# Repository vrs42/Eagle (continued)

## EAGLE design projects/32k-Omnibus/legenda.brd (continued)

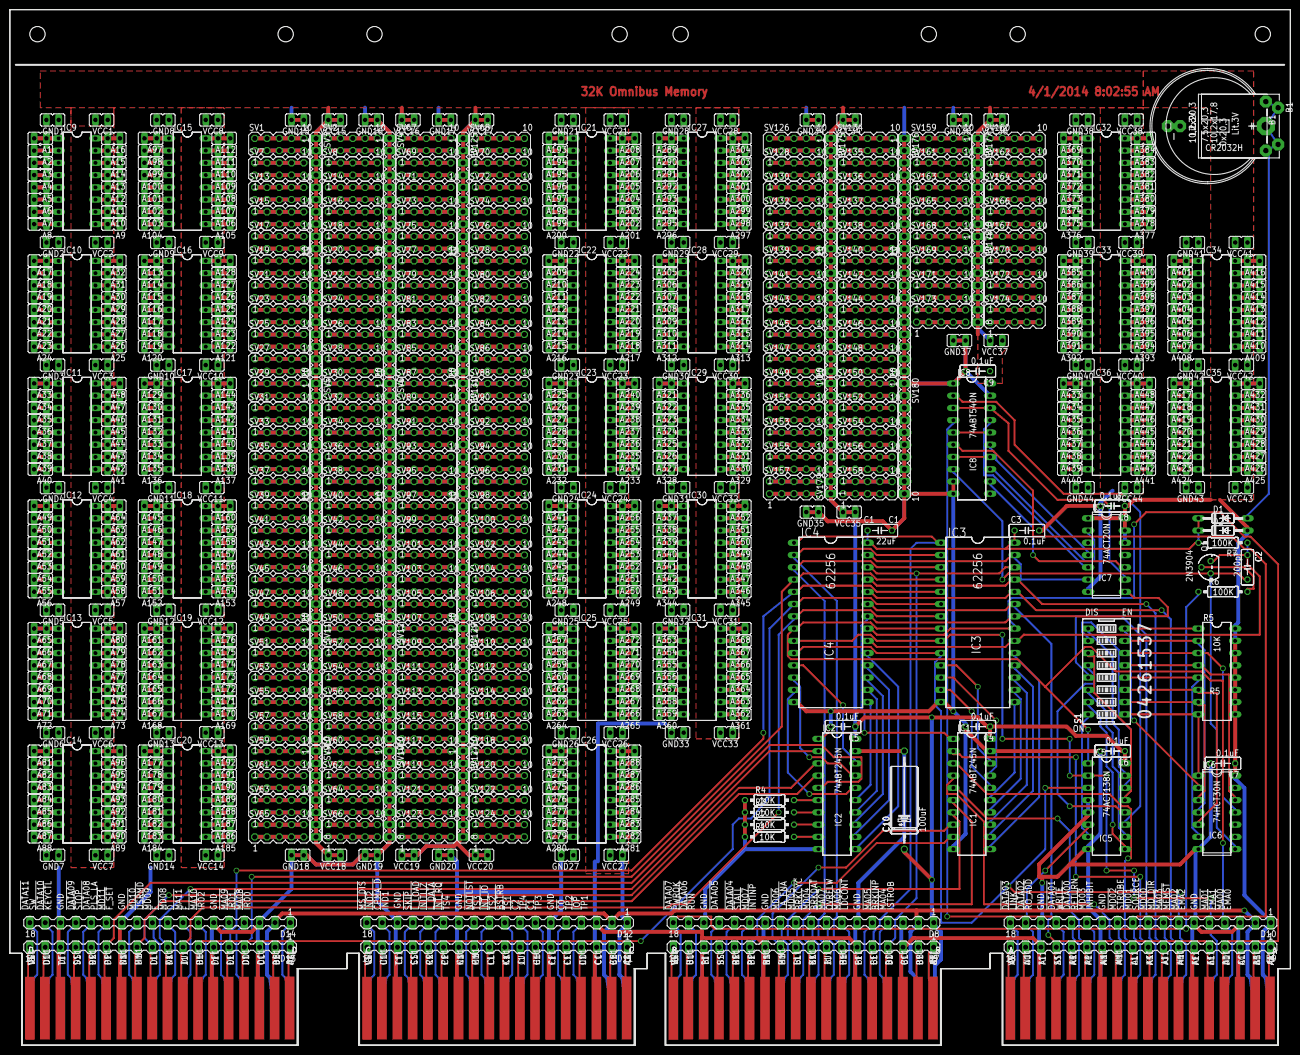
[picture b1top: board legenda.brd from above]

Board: 2 copper layers, 265.4 x 214.6 mm, 784 parts (0 on the bottom side), 930 nets.

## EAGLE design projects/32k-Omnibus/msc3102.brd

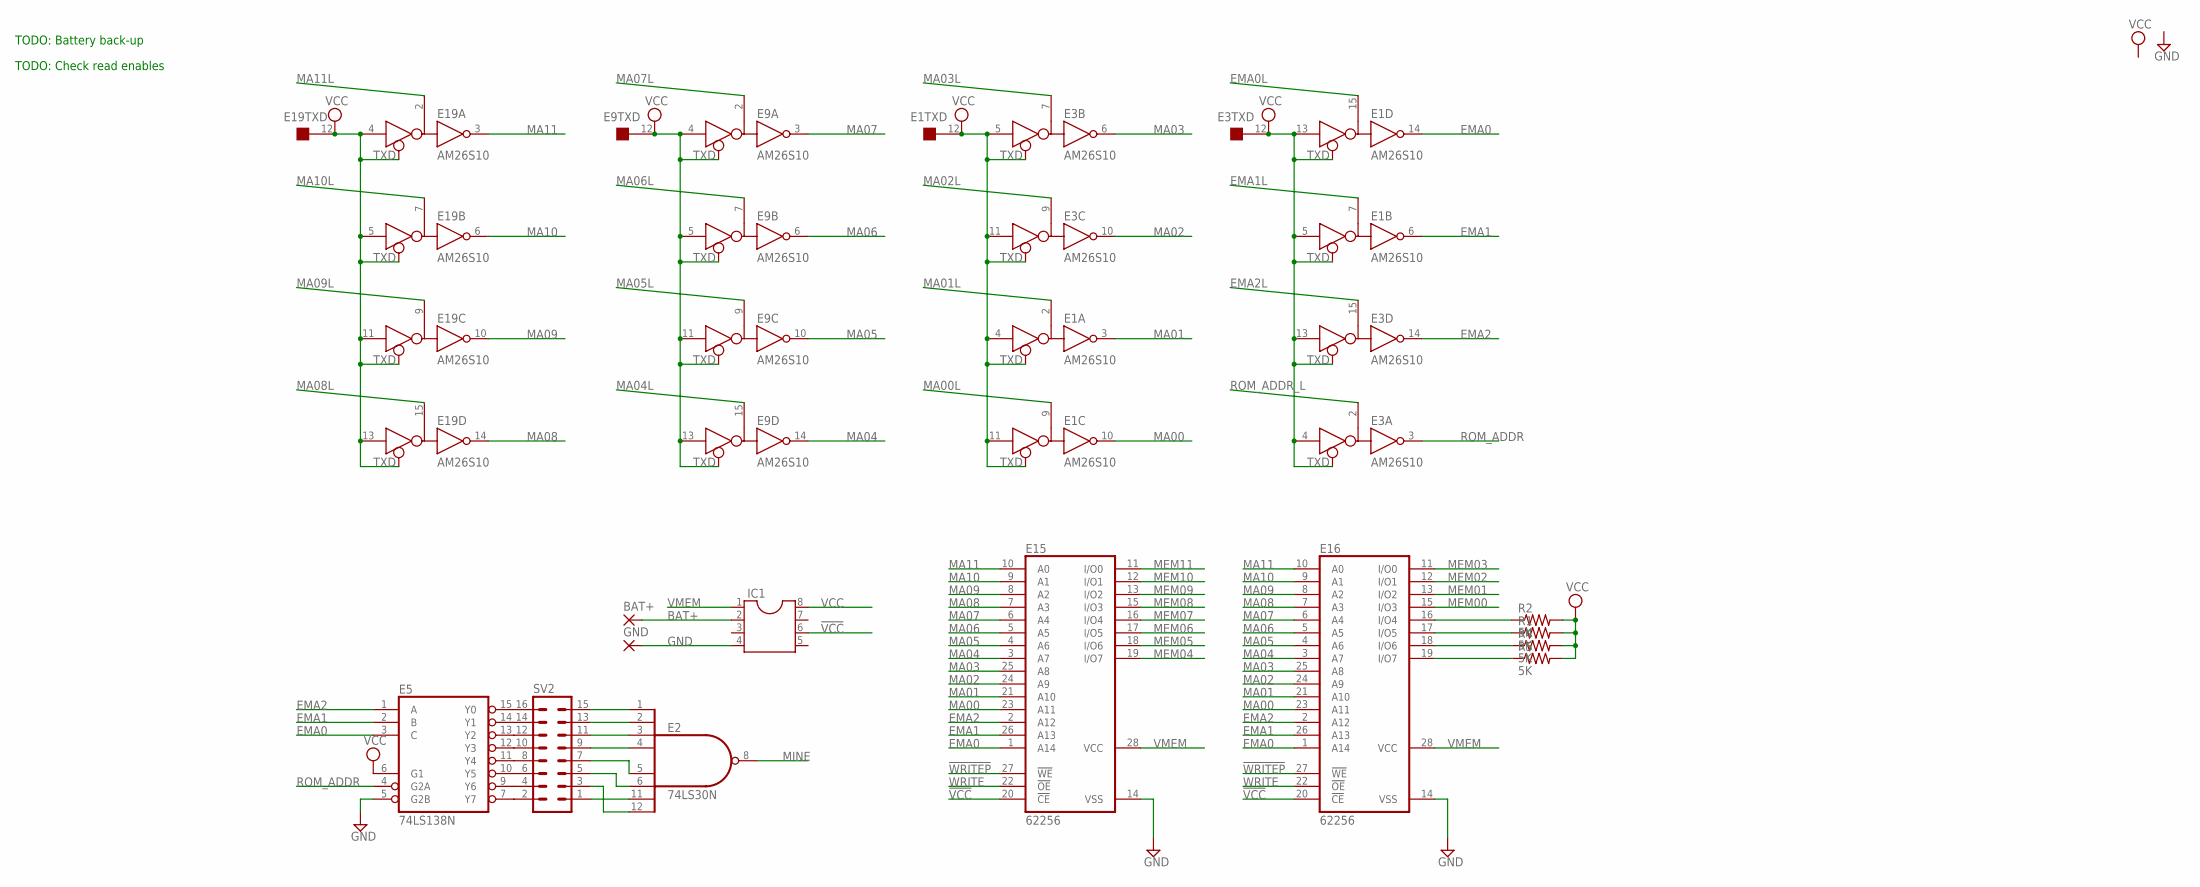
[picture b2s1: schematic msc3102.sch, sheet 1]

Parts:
BAT+: 2,15/1,0
E1, E3, E9, E19: AM26S10; DIL16
E2: 74LS30N; DIL14
E5: 74LS138N; DIL16
E15, E16: 62256; DIL28-6
GND: 2,15/1,0
IC1: DIL8; DIL08
R1, R2, R4, R5: 5K; 0207/10
SV2: MA08-2

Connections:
!VCC: E15.20 (!CE), E16.20 (!CE), IC1.6
!WRITEP: E15.27 (!WE), E16.27 (!WE); also elsewhere on the board
BAT+: BAT+.1, IC1.2
EMA0: E1.14 (R), E5.3 (C), E15.1 (A14), E16.1 (A14)
EMA0L: E1.15 (B); also elsewhere on the board
EMA1: E1.6 (R), E5.2 (B), E15.26 (A13), E16.26 (A13)
EMA1L: E1.7 (B); also elsewhere on the board
EMA2: E3.14 (R), E5.1 (A), E15.2 (A12), E16.2 (A12)
EMA2L: E3.15 (B); also elsewhere on the board
GND: E1.1 (GND), E1.8 (GND), E2.7 (GND), E3.1 (GND), E3.8 (GND), E5.5 (G2B), E5.8 (GND), E9.1 (GND), E9.8 (GND), E15.14 (VSS), E16.14 (VSS), E19.1 (GND), E19.8 (GND), GND.1, IC1.4; also elsewhere on the board
MA00: E1.10 (R), E15.23 (A11), E16.23 (A11)
MA00L: E1.9 (B); also elsewhere on the board
MA01: E1.3 (R), E15.21 (A10), E16.21 (A10)
MA01L: E1.2 (B); also elsewhere on the board
MA02: E3.10 (R), E15.24 (A9), E16.24 (A9)
MA02L: E3.9 (B); also elsewhere on the board
MA03: E3.6 (R), E15.25 (A8), E16.25 (A8)
MA03L: E3.7 (B); also elsewhere on the board
MA04: E9.14 (R), E15.3 (A7), E16.3 (A7)
MA04L: E9.15 (B); also elsewhere on the board
MA05: E9.10 (R), E15.4 (A6), E16.4 (A6)
MA05L: E9.9 (B); also elsewhere on the board
MA06: E9.6 (R), E15.5 (A5), E16.5 (A5)
MA06L: E9.7 (B); also elsewhere on the board
MA07: E9.3 (R), E15.6 (A4), E16.6 (A4)
MA07L: E9.2 (B); also elsewhere on the board
MA08: E15.7 (A3), E16.7 (A3), E19.14 (R)
MA08L: E19.15 (B); also elsewhere on the board
MA09: E15.8 (A2), E16.8 (A2), E19.10 (R)
MA09L: E19.9 (B); also elsewhere on the board
MA10: E15.9 (A1), E16.9 (A1), E19.6 (R)
MA10L: E19.7 (B); also elsewhere on the board
MA11: E15.10 (A0), E16.10 (A0), E19.3 (R)
MA11L: E19.2 (B); also elsewhere on the board
MEM00: E16.15 (I/O3); also elsewhere on the board
MEM01: E16.13 (I/O2); also elsewhere on the board
MEM02: E16.12 (I/O1); also elsewhere on the board
MEM03: E16.11 (I/O0); also elsewhere on the board
MEM04: E15.19 (I/O7); also elsewhere on the board
MEM05: E15.18 (I/O6); also elsewhere on the board
MEM06: E15.17 (I/O5); also elsewhere on the board
MEM07: E15.16 (I/O4); also elsewhere on the board
MEM08: E15.15 (I/O3); also elsewhere on the board
MEM09: E15.13 (I/O2); also elsewhere on the board
MEM10: E15.12 (I/O1); also elsewhere on the board
MEM11: E15.11 (I/O0); also elsewhere on the board
MINE: E2.8 (O); also elsewhere on the board
unnamed: E5.7 (Y7), SV2.2
unnamed: E5.9 (Y6), SV2.4
unnamed: E5.10 (Y5), SV2.6
unnamed: E5.11 (Y4), SV2.8
unnamed: E5.12 (Y3), SV2.10
unnamed: E5.13 (Y2), SV2.12
unnamed: E5.14 (Y1), SV2.14
unnamed: E5.15 (Y0), SV2.16
unnamed: E2.4 (I3), SV2.9
unnamed: E2.3 (I2), SV2.11
unnamed: E2.2 (I1), SV2.13
unnamed: E2.1 (I0), SV2.15
unnamed: E2.5 (I4), SV2.7
unnamed: E2.11 (I6), SV2.1
unnamed: E2.12 (I7), SV2.3
unnamed: E2.6 (I5), SV2.5
unnamed: E16.18 (I/O6), R4.1
unnamed: E16.16 (I/O4), R2.1
unnamed: E16.17 (I/O5), R1.1
unnamed: E16.19 (I/O7), R5.1
ROM_ADDR: E3.3 (R), E5.4 (G2A)
ROM_ADDR_L: E3.2 (B); also elsewhere on the board
VCC: E1.4 (D), E1.5 (D), E1.11 (D), E1.12 (TXD), E1.13 (D), E1.16 (VCC), E2.14 (VCC), E3.4 (D), E3.5 (D), E3.11 (D), E3.12 (TXD), E3.13 (D), E3.16 (VCC), E5.6 (G1), E5.16 (VCC), E9.4 (D), E9.5 (D), E9.11 (D), E9.12 (TXD), E9.13 (D), E9.16 (VCC), E19.4 (D), E19.5 (D), E19.11 (D), E19.12 (TXD), E19.13 (D), E19.16 (VCC), IC1.8, R1.2, R2.2, R4.2, R5.2; also elsewhere on the board
VMEM: E15.28 (VCC), E16.28 (VCC), IC1.1
WRITE: E15.22 (!OE), E16.22 (!OE); also elsewhere on the board

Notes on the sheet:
TODO: Battery back-up
TODO: Check read enables

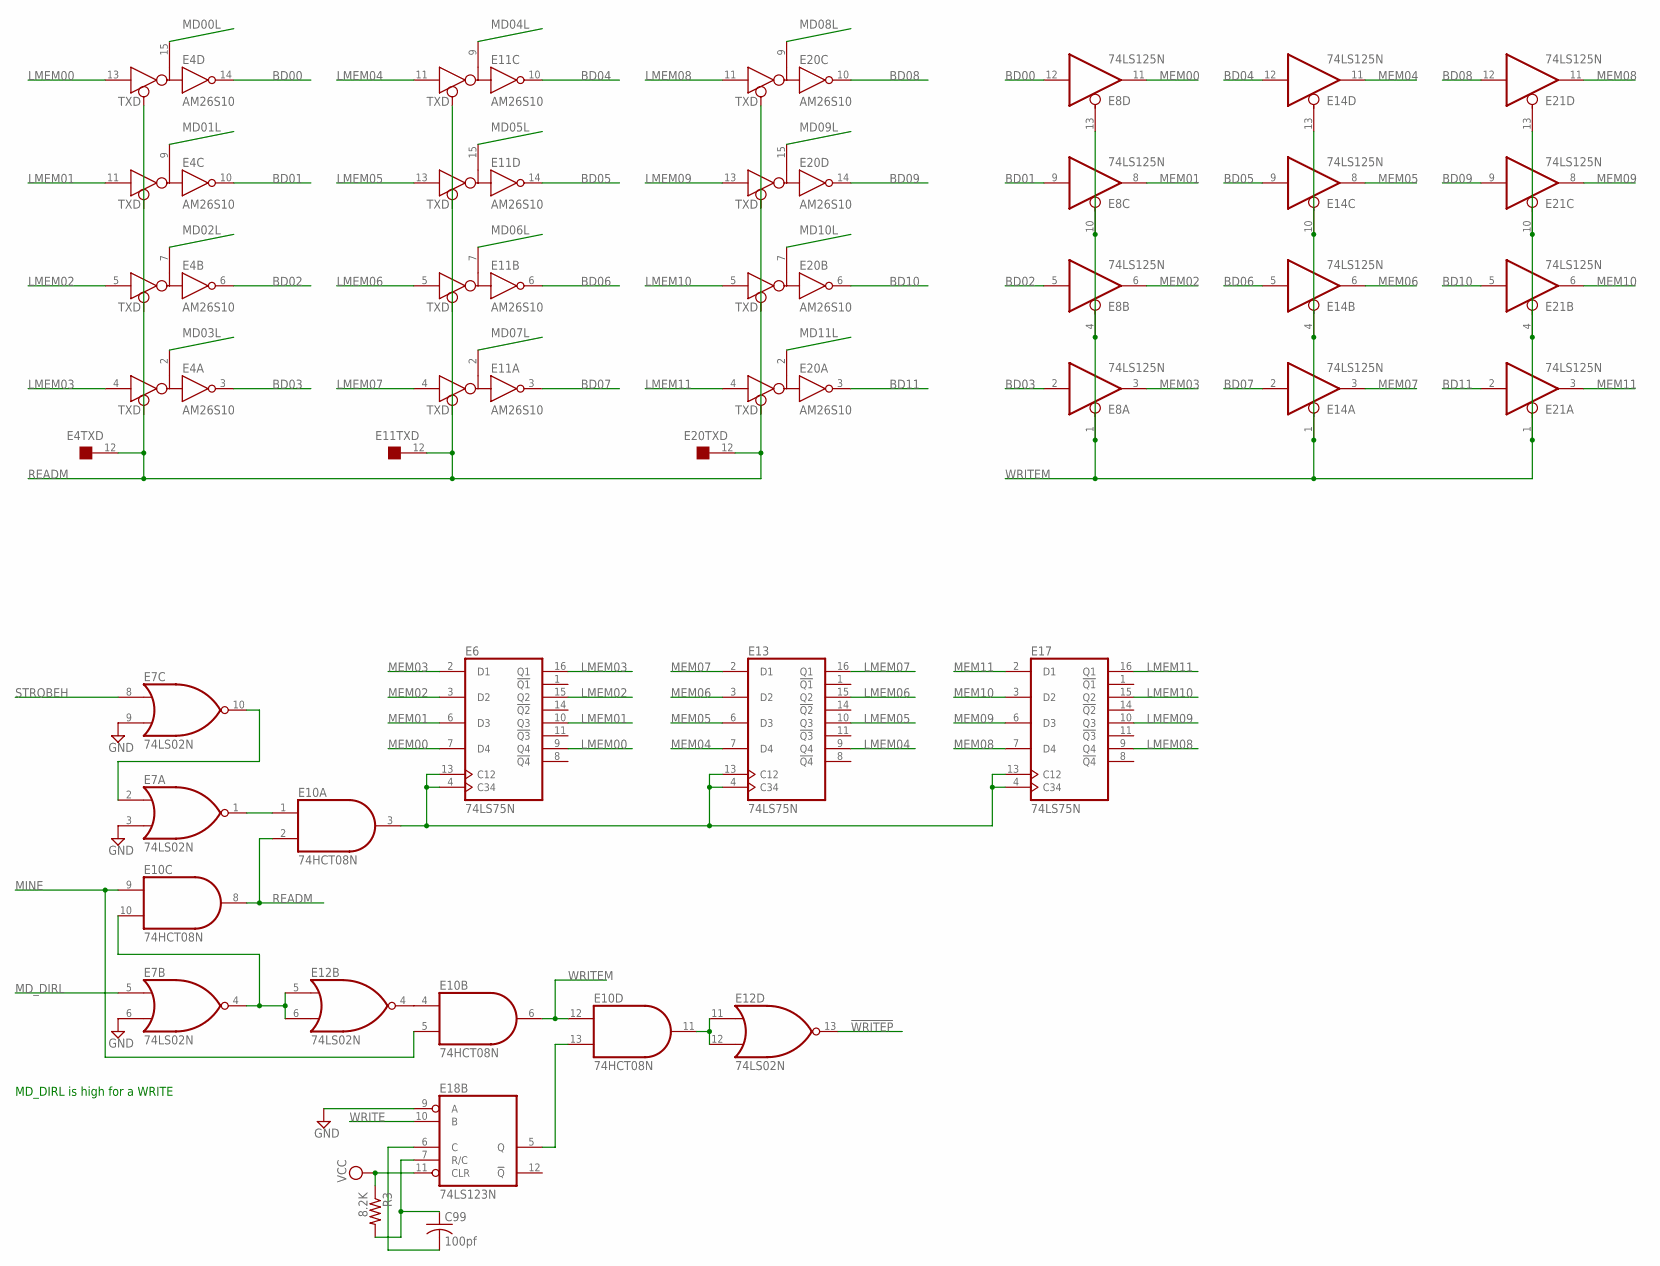
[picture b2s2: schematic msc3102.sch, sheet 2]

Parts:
C99: 100pf; C050-025X075
E4, E11, E20: AM26S10; DIL16
E6, E13, E17: 74LS75N; DIL16
E7, E12: 74LS02N; DIL14
E8, E14, E21: 74LS125N; DIL14
E10: 74HCT08N; DIL14
E18: 74LS123N; DIL16
R3: 8.2K; 0207/10

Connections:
!WRITEP: E12.13 (O); also elsewhere on the board
BD00: E4.14 (R), E8.12 (I)
BD01: E4.10 (R), E8.9 (I)
BD02: E4.6 (R), E8.5 (I)
BD03: E4.3 (R), E8.2 (I)
BD04: E11.10 (R), E14.12 (I)
BD05: E11.14 (R), E14.9 (I)
BD06: E11.6 (R), E14.5 (I)
BD07: E11.3 (R), E14.2 (I)
BD08: E20.10 (R), E21.12 (I)
BD09: E20.14 (R), E21.9 (I)
BD10: E20.6 (R), E21.5 (I)
BD11: E20.3 (R), E21.2 (I)
GND: E4.1 (GND), E4.8 (GND), E6.12 (GND), E7.3 (I1), E7.6 (I1), E7.7 (GND), E7.9 (I1), E8.7 (GND), E10.7 (GND), E11.1 (GND), E11.8 (GND), E12.7 (GND), E13.12 (GND), E14.7 (GND), E17.12 (GND), E18.8 (GND), E18.9 (A), E20.1 (GND), E20.8 (GND), E21.7 (GND); also elsewhere on the board
LMEM00: E4.13 (D), E6.9 (Q4)
LMEM01: E4.11 (D), E6.10 (Q3)
LMEM02: E4.5 (D), E6.15 (Q2)
LMEM03: E4.4 (D), E6.16 (Q1)
LMEM04: E11.11 (D), E13.9 (Q4)
LMEM05: E11.13 (D), E13.10 (Q3)
LMEM06: E11.5 (D), E13.15 (Q2)
LMEM07: E11.4 (D), E13.16 (Q1)
LMEM08: E17.9 (Q4), E20.11 (D)
LMEM09: E17.10 (Q3), E20.13 (D)
LMEM10: E17.15 (Q2), E20.5 (D)
LMEM11: E17.16 (Q1), E20.4 (D)
MD00L: E4.15 (B); also elsewhere on the board
MD01L: E4.9 (B); also elsewhere on the board
MD02L: E4.7 (B); also elsewhere on the board
MD03L: E4.2 (B); also elsewhere on the board
MD04L: E11.9 (B); also elsewhere on the board
MD05L: E11.15 (B); also elsewhere on the board
MD06L: E11.7 (B); also elsewhere on the board
MD07L: E11.2 (B); also elsewhere on the board
MD08L: E20.9 (B); also elsewhere on the board
MD09L: E20.15 (B); also elsewhere on the board
MD10L: E20.7 (B); also elsewhere on the board
MD11L: E20.2 (B); also elsewhere on the board
MD_DIRL: E7.5 (I0); also elsewhere on the board
MEM00: E6.7 (D4), E8.11 (O); also elsewhere on the board
MEM01: E6.6 (D3), E8.8 (O); also elsewhere on the board
MEM02: E6.3 (D2), E8.6 (O); also elsewhere on the board
MEM03: E6.2 (D1), E8.3 (O); also elsewhere on the board
MEM04: E13.7 (D4), E14.11 (O); also elsewhere on the board
MEM05: E13.6 (D3), E14.8 (O); also elsewhere on the board
MEM06: E13.3 (D2), E14.6 (O); also elsewhere on the board
MEM07: E13.2 (D1), E14.3 (O); also elsewhere on the board
MEM08: E17.7 (D4), E21.11 (O); also elsewhere on the board
MEM09: E17.6 (D3), E21.8 (O); also elsewhere on the board
MEM10: E17.3 (D2), E21.6 (O); also elsewhere on the board
MEM11: E17.2 (D1), E21.3 (O); also elsewhere on the board
MINE: E10.5 (I1), E10.9 (I0); also elsewhere on the board
unnamed: C99.1, E18.7 (R/C), R3.2
unnamed: C99.2, E18.6 (C)
unnamed: E10.4 (I0), E12.4 (O)
unnamed: E7.4 (O), E10.10 (I1), E12.5 (I0), E12.6 (I1)
unnamed: E7.1 (O), E10.1 (I0)
unnamed: E7.2 (I0), E7.10 (O)
unnamed: E6.4 (C34), E6.13 (C12), E10.3 (O), E13.4 (C34), E13.13 (C12), E17.4 (C34), E17.13 (C12)
unnamed: E10.13 (I1), E18.5 (Q)
unnamed: E10.11 (O), E12.11 (I0), E12.12 (I1)
READM: E4.12 (TXD), E10.2 (I1), E10.8 (O), E11.12 (TXD), E20.12 (TXD)
STROBEH: E7.8 (I0); also elsewhere on the board
VCC: E4.16 (VCC), E6.5 (VCC), E7.14 (VCC), E8.14 (VCC), E10.14 (VCC), E11.16 (VCC), E12.14 (VCC), E13.5 (VCC), E14.14 (VCC), E17.5 (VCC), E18.11 (CLR), E18.16 (VCC), E20.16 (VCC), E21.14 (VCC), R3.1; also elsewhere on the board
WRITE: E18.10 (B); also elsewhere on the board
WRITEM: E8.1 (OE), E8.4 (OE), E8.10 (OE), E8.13 (OE), E10.6 (O), E10.12 (I0), E14.1 (OE), E14.4 (OE), E14.10 (OE), E14.13 (OE), E21.1 (OE), E21.4 (OE), E21.10 (OE), E21.13 (OE)

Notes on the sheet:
MD_DIRL is high for a WRITE

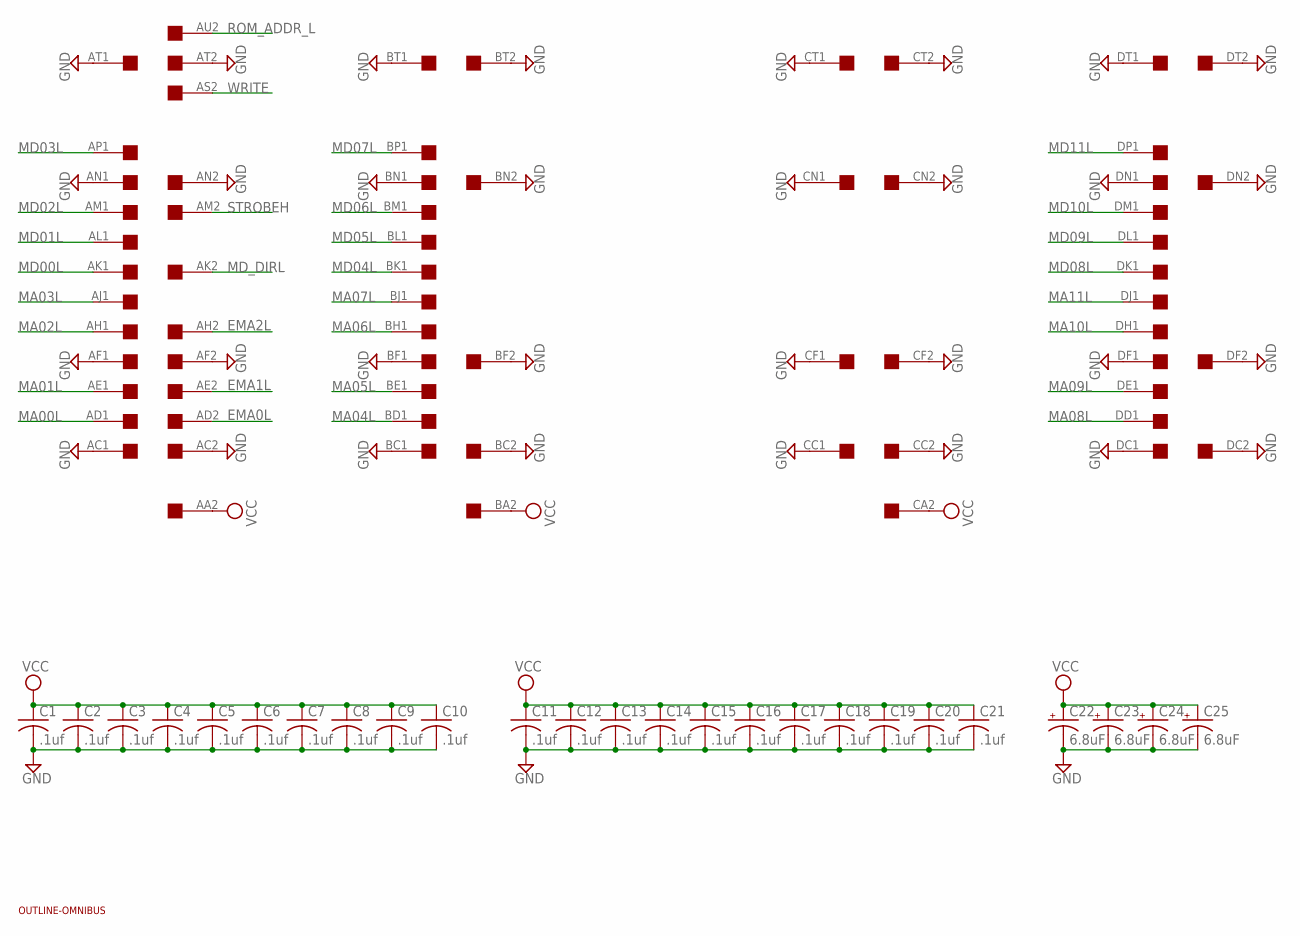
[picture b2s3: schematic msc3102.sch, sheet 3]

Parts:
C1, C2, C3, C4, C5, C6, C7, C8, C9, C10, C11, C12, C13, C14, C15, C16, C17, C18, C19, C20, C21: .1uf; C050-025X075
C22, C23, C24, C25: 6.8uF; E22-6
U$1: OUTLINE-OMNIBUS; OMNIBUS
U$2: QUAD; EDGE-CON8

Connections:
EMA0L: U$2.AD2; also elsewhere on the board
EMA1L: U$2.AE2; also elsewhere on the board
EMA2L: U$2.AH2; also elsewhere on the board
GND: C1.2, C2.2, C3.2, C4.2, C5.2, C6.2, C7.2, C8.2, C9.2, C10.2, C11.2, C12.2, C13.2, C14.2, C15.2, C16.2, C17.2, C18.2, C19.2, C20.2, C21.2, C22.-, C23.-, C24.-, C25.-, U$2.AC1, U$2.AC2, U$2.AF1, U$2.AF2, U$2.AN1, U$2.AN2, U$2.AT1, U$2.AT2, U$2.BC1, U$2.BC2, U$2.BF1, U$2.BF2, U$2.BN1, U$2.BN2, U$2.BT1, U$2.BT2, U$2.CC1, U$2.CC2, U$2.CF1, U$2.CF2, U$2.CN1, U$2.CN2, U$2.CT1, U$2.CT2, U$2.DC1, U$2.DC2, U$2.DF1, U$2.DF2, U$2.DN1, U$2.DN2, U$2.DT1, U$2.DT2; also elsewhere on the board
MA00L: U$2.AD1; also elsewhere on the board
MA01L: U$2.AE1; also elsewhere on the board
MA02L: U$2.AH1; also elsewhere on the board
MA03L: U$2.AJ1; also elsewhere on the board
MA04L: U$2.BD1; also elsewhere on the board
MA05L: U$2.BE1; also elsewhere on the board
MA06L: U$2.BH1; also elsewhere on the board
MA07L: U$2.BJ1; also elsewhere on the board
MA08L: U$2.DD1; also elsewhere on the board
MA09L: U$2.DE1; also elsewhere on the board
MA10L: U$2.DH1; also elsewhere on the board
MA11L: U$2.DJ1; also elsewhere on the board
MD00L: U$2.AK1; also elsewhere on the board
MD01L: U$2.AL1; also elsewhere on the board
MD02L: U$2.AM1; also elsewhere on the board
MD03L: U$2.AP1; also elsewhere on the board
MD04L: U$2.BK1; also elsewhere on the board
MD05L: U$2.BL1; also elsewhere on the board
MD06L: U$2.BM1; also elsewhere on the board
MD07L: U$2.BP1; also elsewhere on the board
MD08L: U$2.DK1; also elsewhere on the board
MD09L: U$2.DL1; also elsewhere on the board
MD10L: U$2.DM1; also elsewhere on the board
MD11L: U$2.DP1; also elsewhere on the board
MD_DIRL: U$2.AK2; also elsewhere on the board
ROM_ADDR_L: U$2.AU2; also elsewhere on the board
STROBEH: U$2.AM2; also elsewhere on the board
VCC: C1.1, C2.1, C3.1, C4.1, C5.1, C6.1, C7.1, C8.1, C9.1, C10.1, C11.1, C12.1, C13.1, C14.1, C15.1, C16.1, C17.1, C18.1, C19.1, C20.1, C21.1, C22.+, C23.+, C24.+, C25.+, U$2.AA2, U$2.BA2, U$2.CA2; also elsewhere on the board
WRITE: U$2.AS2; also elsewhere on the board

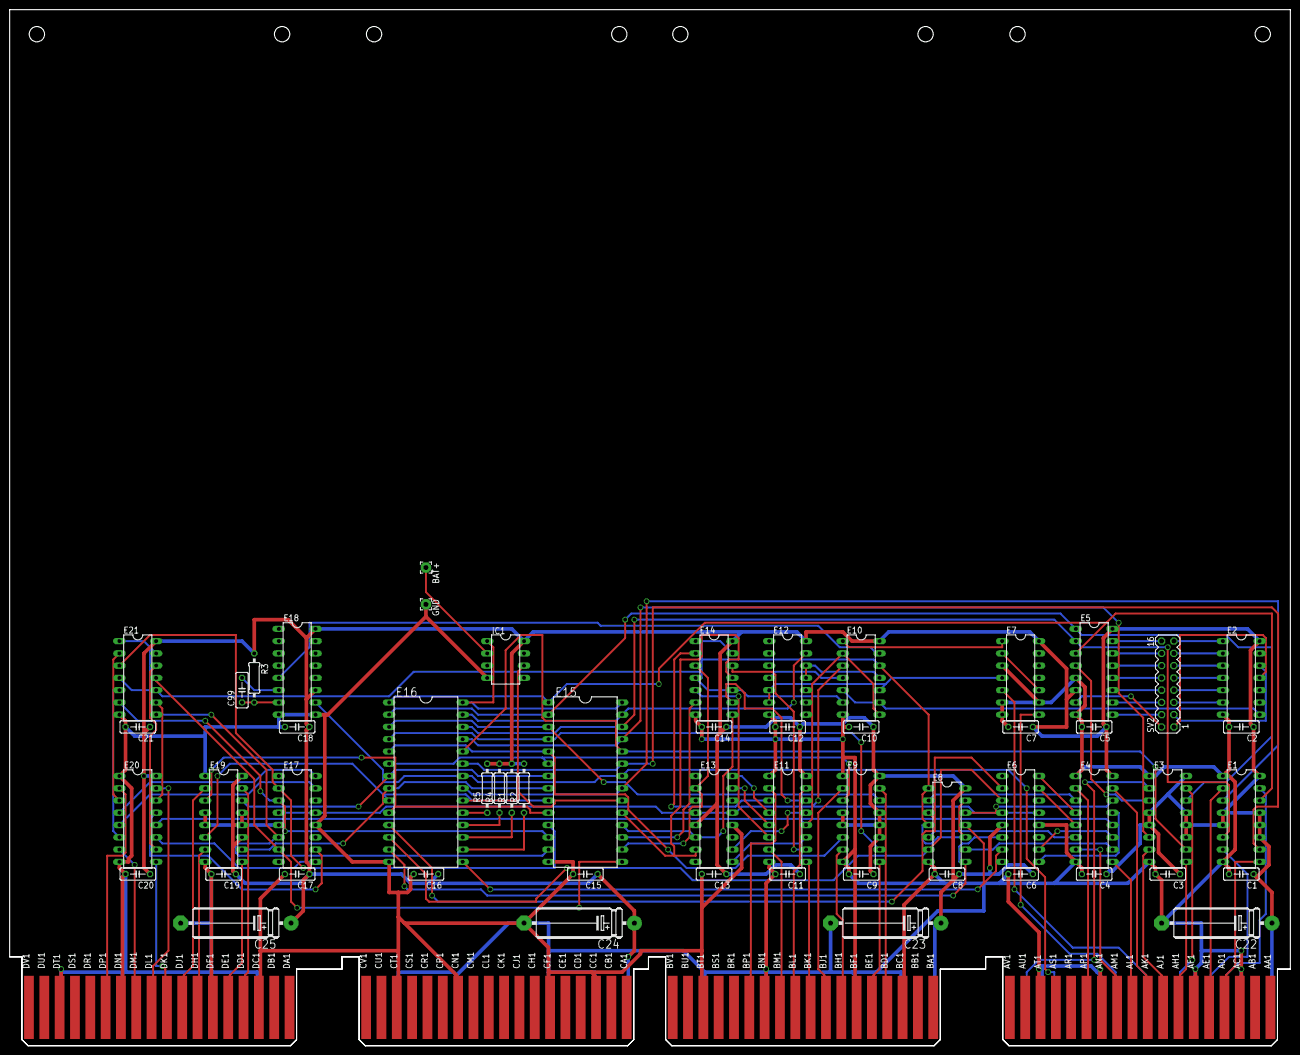
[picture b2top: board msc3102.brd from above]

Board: 2 copper layers, 265.3 x 214.6 mm, 58 parts (0 on the bottom side), 121 nets.

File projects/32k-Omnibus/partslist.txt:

Partlist

Exported from msc3102.brd at 11/08/2006 05:23:20p

EAGLE Version 4.11 Copyright (c) 1988-2003 CadSoft

Part     Value          Package      Library        Position (inch)       Orientation

BAT+                    2,15/1,0     wirepad        (3.4 3.9)             R270
C1       .1uf           C050-025X075 rcl            (10.05 1.4)           R180
C2       .1uf           C050-025X075 rcl            (10.05 2.6)           R180
C3       .1uf           C050-025X075 rcl            (9.45 1.4)            R180
C4       .1uf           C050-025X075 rcl            (8.85 1.4)            R180
C5       .1uf           C050-025X075 rcl            (8.85 2.6)            R180
C6       .1uf           C050-025X075 rcl            (8.25 1.4)            R180
C7       .1uf           C050-025X075 rcl            (8.25 2.6)            R180
C8       .1uf           C050-025X075 rcl            (7.65 1.4)            R180
C9       .1uf           C050-025X075 rcl            (6.95 1.4)            R180
C10      .1uf           C050-025X075 rcl            (6.95 2.6)            R180
C11      .1uf           C050-025X075 rcl            (6.35 1.4)            R180
C12      .1uf           C050-025X075 rcl            (6.35 2.6)            R180
C13      .1uf           C050-025X075 rcl            (5.75 1.4)            R180
C14      .1uf           C050-025X075 rcl            (5.75 2.6)            R180
C15      .1uf           C050-025X075 rcl            (4.7 1.4)             R180
C16      .1uf           C050-025X075 rcl            (3.4 1.4)             R180
C17      .1uf           C050-025X075 rcl            (2.35 1.4)            R180
C18      .1uf           C050-025X075 rcl            (2.35 2.6)            R180
C19      .1uf           C050-025X075 rcl            (1.75 1.4)            R180
C20      .1uf           C050-025X075 rcl            (1.05 1.4)            R180
C21      .1uf           C050-025X075 rcl            (1.05 2.6)            R180
C22                     E22-6        rcl            (9.85 1)              R180
C23                     E22-6        rcl            (7.15 1)              R180
C24                     E22-6        rcl            (4.65 1)              R180
C25                     E22-6        rcl            (1.85 0.9)            R180
C99      100pf          C050-025X075 rcl            (1.9 2.9)             R90
E1       AM26S10        DIL16        dec-con        (10.05 1.85)          R270
E2       74LS30N        DIL14        74xx-jameco    (10.05 3)             R270
E3       AM26S10        DIL16        dec-con        (9.45 1.85)           R270
E4       AM26S10        DIL16        dec-con        (8.85 1.85)           R270
E5       74HCT138N      DIL16        74xx-jameco    (8.85 3.05)           R270
E6       74LS75N        DIL16        74xx-jameco    (8.25 1.85)           R270
E7       74HCT02N       DIL14        74xx-jameco    (8.25 3)              R270
E8       74LS125N       DIL14        74xx-jameco    (7.65 1.8)            R270
E9       AM26S10        DIL16        dec-con        (6.95 1.85)           R270
E10      74HCT08N       DIL14        74xx-jameco    (6.95 3)              R270
E11      AM26S10        DIL16        dec-con        (6.35 1.85)           R270
E12      74HCT02N       DIL14        74xx-jameco    (6.35 3)              R270
E13      74LS75N        DIL16        74xx-jameco    (5.75 1.85)           R270
E14      74LS125N       DIL14        74xx-jameco    (5.75 3)              R270
E15      62256          DIL28-6      memory-hitachi (4.7 2.15)            R270
E16      62256          DIL28-6      memory-hitachi (3.4 2.15)            R270
E17      74LS75N        DIL16        74xx-jameco    (2.35 1.85)           R270
E18      74HCT123N      DIL16        74xx-jameco    (2.35 3.05)           R270
E19      AM26S10        DIL16        dec-con        (1.75 1.85)           R270
E20      AM26S10        DIL16        dec-con        (1.05 1.85)           R270
E21      74LS125N       DIL14        74xx-jameco    (1.05 3)              R270
GND                     2,15/1,0     wirepad        (3.4 3.6)             R270
IC1                     DIL08        ic-package     (4.05 3.15)           R270
R1       5K             0207/10      rcl            (4.1 2.1)             R90
R2       5K             0207/10      rcl            (4.2 2.1)             R90
R3       8.2K           0207/10      rcl            (2 3)                 R270
R4       5K             0207/10      rcl            (4 2.1)               R90
R5       5K             0207/10      rcl            (3.9 2.1)             R90
SV2                     MA08-2       con-lstb       (9.45 2.95)           R90
U$2                     EDGE-CON8    dec-con        (0 0)                 R0

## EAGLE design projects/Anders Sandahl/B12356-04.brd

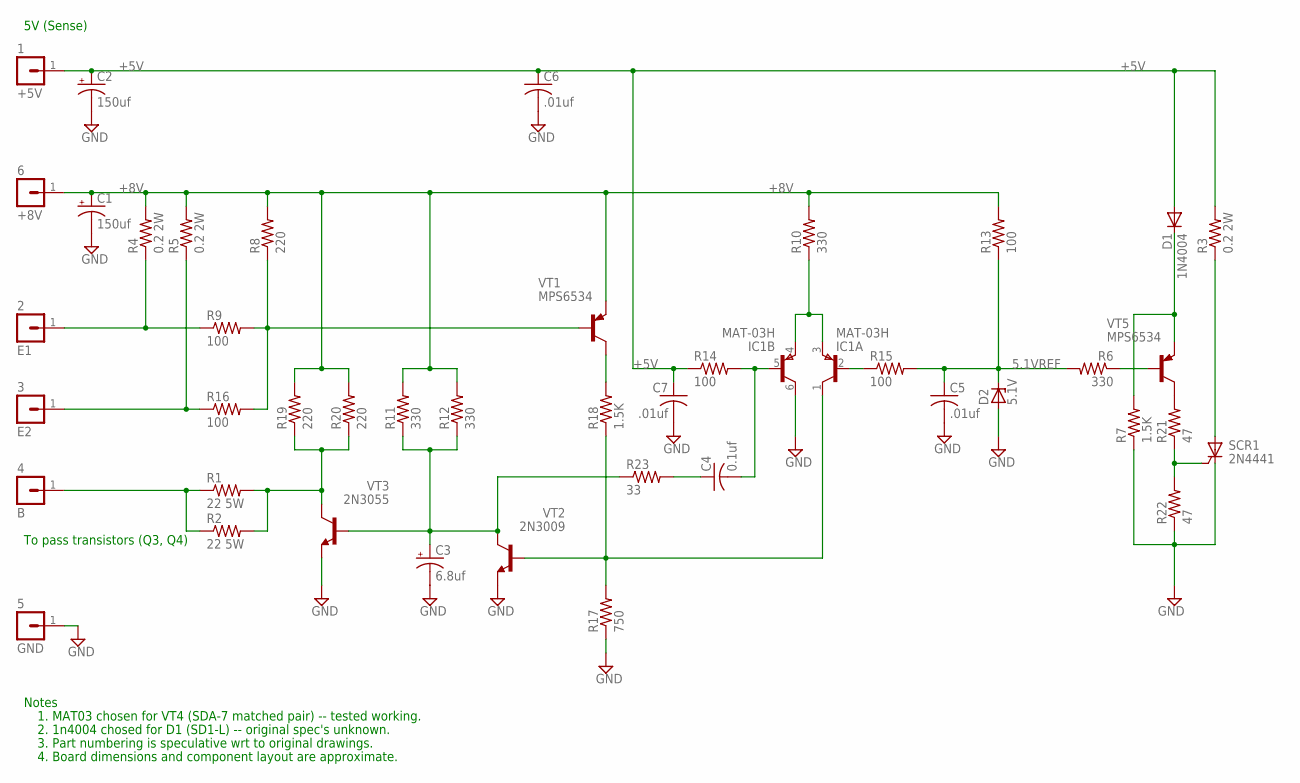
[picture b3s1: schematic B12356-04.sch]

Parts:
+5V: 1; SPADELUG
+8V: 6; SPADELUG
B: 4; SPADELUG
C1, C2: 150uf; E22-6
C3: 6.8uf; E15-5
C4: 0.1uf; C102-064X133
C5, C6, C7: .01uf; C050-025X075
D1: 1N4004; DO41-10
D2: 5.1V; DO41Z10
E1: 2; SPADELUG
E2: 3; SPADELUG
GND: 5; SPADELUG
IC1: MAT-03H; TO78
R1, R2: 22 5W; P0817/22
R3, R4, R5: 0.2 2W; 0414/15
R6, R10, R11, R12: 330; 0207/10
R7, R18: 1.5K; 0207/10
R8, R19, R20: 220; 0207/10
R9, R13, R14, R15, R16: 100; 0207/10
R17: 750; 0207/10
R21, R22: 47; 0207/10
R23: 33; 0207/10
SCR1: 2N4441; TO220CL
VT1, VT5: MPS6534; TO92-BCE
VT2: 2N3009; TO18
VT3: 2N3055; TO3

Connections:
5.1VREF: C5.1, D2.C, R6.2, R13.1, R15.2
+5V: +5V.1, C2.+, C6.1, C7.1, D1.A, R3.2, R14.1
+8V: +8V.1, C1.+, R4.2, R5.2, R8.2, R10.2, R11.2, R12.2, R13.2, R19.2, R20.2, VT1.E
GND: C1.-, C2.-, C3.-, C5.2, C6.2, C7.2, D2.A, GND.1, IC1.6 (C), R7.1, R17.1, R22.1, SCR1.C, VT2.1 (E), VT3.E
unnamed: IC1.2 (B), R15.1
unnamed: IC1.3 (E), IC1.4 (E), R10.1
unnamed: R3.1, SCR1.A
unnamed: R21.1, R22.2, SCR1.G
unnamed: E1.1, R4.1, R9.1
unnamed: E2.1, R5.1, R16.1
unnamed: R8.1, R9.2, R16.2, VT1.B
unnamed: R21.2, VT5.C
unnamed: D1.C, R7.2, VT5.E
unnamed: R6.1, VT5.B
unnamed: IC1.1 (C), R17.2, R18.1, VT2.2 (B)
unnamed: B.1, R1.1, R2.1
unnamed: R18.2, VT1.C
unnamed: C3.+, R11.1, R12.1, R23.1, VT2.3 (C), VT3.B
unnamed: R1.2, R2.2, R19.1, R20.1, VT3.C, VT3.C/ (C)
unnamed: C4.2, IC1.5 (B), R14.2
unnamed: C4.1, R23.2

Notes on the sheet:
To pass transistors (Q3, Q4)
5V (Sense)
1. MAT03 chosen for VT4 (SDA-7 matched pair) -- tested working.
Notes
2. 1n4004 chosed for D1 (SD1-L) -- original spec's unknown.
3. Part numbering is speculative wrt to original drawings.
4. Board dimensions and component layout are approximate.

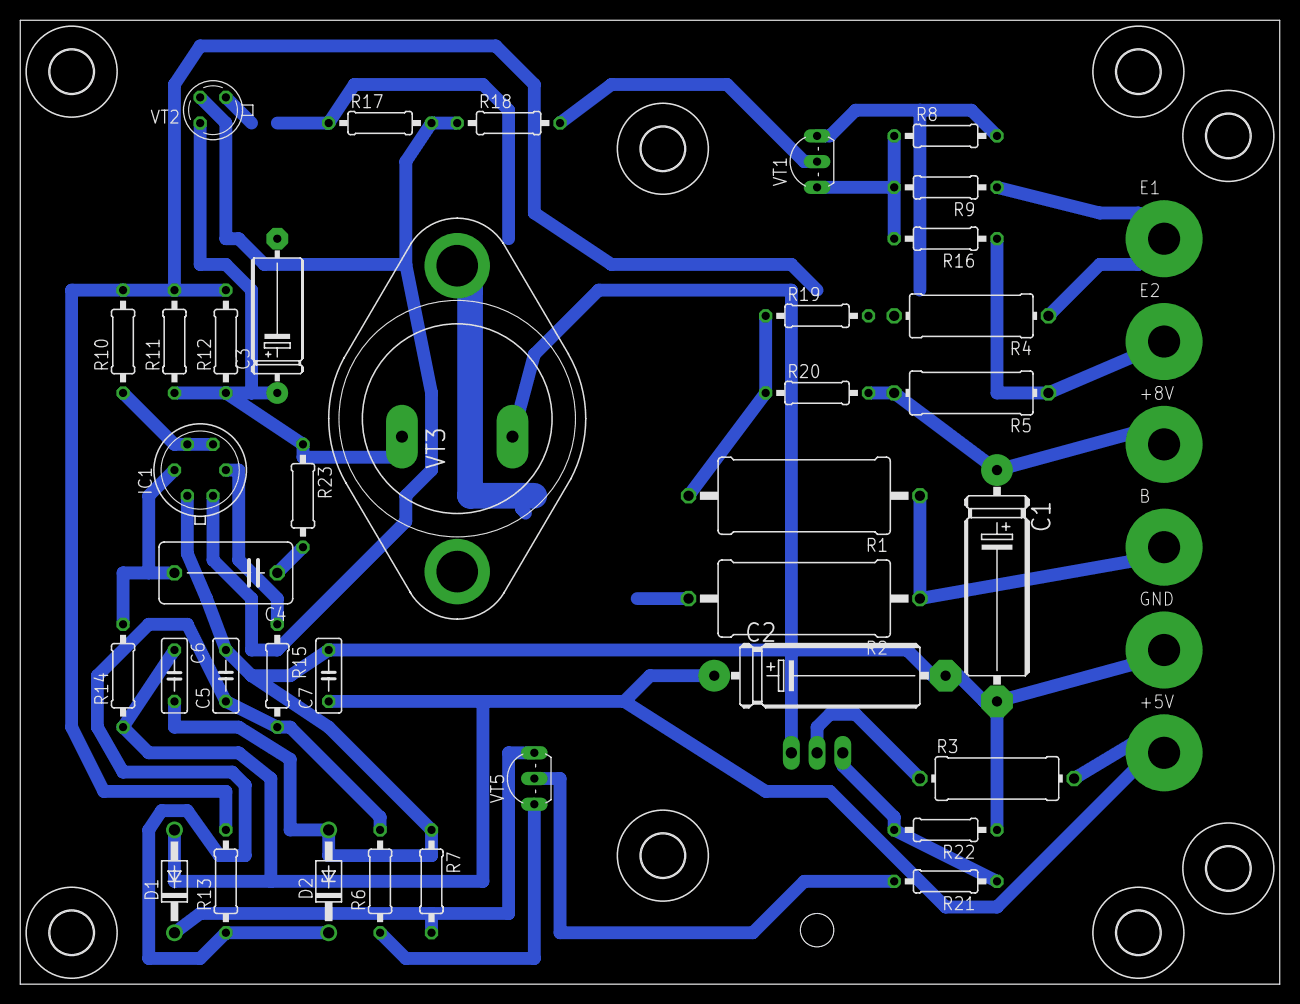
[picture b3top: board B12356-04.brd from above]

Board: 2 copper layers, 124.5 x 95.2 mm, 52 parts (1 on the bottom side), 21 nets.

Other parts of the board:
U$1, U$2, U$3, U$4, U$5, U$6, U$7, U$8: 4,3
